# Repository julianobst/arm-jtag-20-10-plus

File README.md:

# arm-jtag-20-10-plus
KiCad project for ARM Cortex-M JTAG Adapter with 20, 10 and 6 pin target header

The adaptor can be used by a debug probe with a standard [ARM JTAG 20](http://infocenter.arm.com/help/index.jsp?topic=/com.arm.doc.dui0499d/BEHEIHCE.html) connector with 2.54 mm pitch and 2x10 pins. Like SEGGER J-Link, Olimex ARM-USB-TINY, STLINK-V3SET etc.

As target connectors, the adaptor provides a 20 and a 10 pin SWD Cortex debug connector with 1.27 mm pitch (J1, J2) and a simple 6 pin 2.54 mm pitch header for SWD (J3) according to the SWD header of the STM32 Nucleo board.

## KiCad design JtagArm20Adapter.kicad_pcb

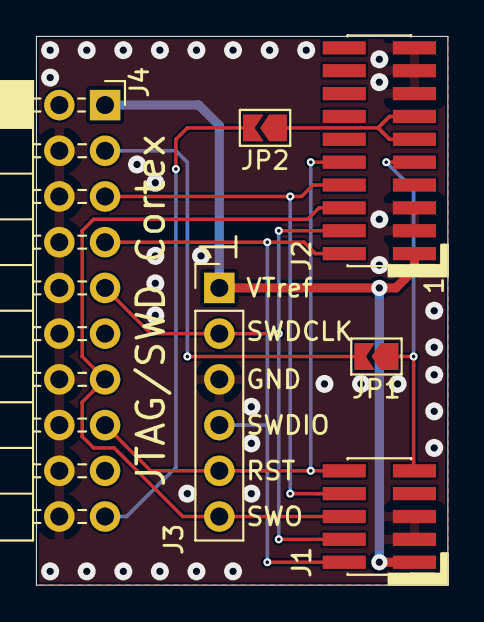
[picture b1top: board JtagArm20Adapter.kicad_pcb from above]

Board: 2 copper layers, 22.9 x 30.5 mm, 6 parts (0 on the bottom side), 11 nets.

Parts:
J1: Conn_02x05_Odd_Even; PinHeader_2x05_P1.27mm_Vertical_SMD
J2: Conn_02x10_Odd_Even; PinHeader_2x10_P1.27mm_Vertical_SMD
J3: Conn_01x06; PinHeader_1x06_P2.54mm_Vertical
J4: Conn_02x10_Odd_Even; PinSocket_2x10_P2.54mm_Horizontal
JP1, JP2: SolderJumper_2_Open; SolderJumper-2_P1.3mm_Open_TrianglePad1.0x1.5mm

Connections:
/DBGACK: J4.19, JP2.2
/RESET: J1.10, J2.10, J3.5, J4.15
/SWDCLK\TCK: J1.4, J2.4, J3.2, J4.9
/SWDIO\TMS: J1.2, J2.2, J3.4, J4.7
/SWO\TDO: J1.6, J2.6, J3.6, J4.13
/TDI: J1.8, J2.8, J4.5
/VTref: J1.1, J2.1, J3.1, J4.1
/nTRST: J4.3, JP1.2
GND: J1.3, J1.5, J2.3, J2.5, J2.15, J2.17, J2.19, J3.3, J4.4, J4.6, J4.8, J4.10, J4.12, J4.14, J4.16, J4.18, J4.20
unnamed: J1.9, J2.9, JP1.1
unnamed: J2.11, J2.13, JP2.1

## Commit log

2020-04-26 First version used for prototype production
2020-04-26 Update README.md and add images of 3D rendered PCBA
2020-05-11 Change J2 from legacy IDC JTAG to Cortex debug pinout
